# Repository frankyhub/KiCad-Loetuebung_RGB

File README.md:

<div align="center">

|[:skull:ISSUE](https://github.com/frankyhub/KiCad-Loetuebung_RGB/issues?q=is%3Aissue)|[:speech_balloon: Forum /Discussion](https://github.com/frankyhub/KiCad-Loetuebung_RGB/discussions)|[:grey_question:WiKi](https://github.com/frankyhub/KiCad-Loetuebung_RGB/wiki)||
|--|--|--|--|
| | | | |
<a href="https://github.com/frankyhub/KiCad-Loetuebung_RGB/issues">|<a href="https://github.com/frankyhub/KiCad-Loetuebung_RGB/discussions">|<a href="https://github.com/frankyhub/KiCad-Loetuebung_RGB/releases">||
|| <a href="https://github.com/frankyhub/KiCad-Loetuebung_RGB/pulse" alt="Activity">| <a href="https://github.com/frankyhub/KiCad-Loetuebung_RGB/graphs/traffic">  |<a href="https://github.com/frankyhub?tab=stars"> ||
</div>

## Fledermaus

## Seegeist

---

<div style="position:absolute; left:2cm; ">   
<ol class="breadcrumb" style="border-top: 2px solid black;border-bottom:2px solid black; height: 45px; width: 900px;"> <p align="center"><a href="#oben">nach oben</a></p></ol>
</div>  

---

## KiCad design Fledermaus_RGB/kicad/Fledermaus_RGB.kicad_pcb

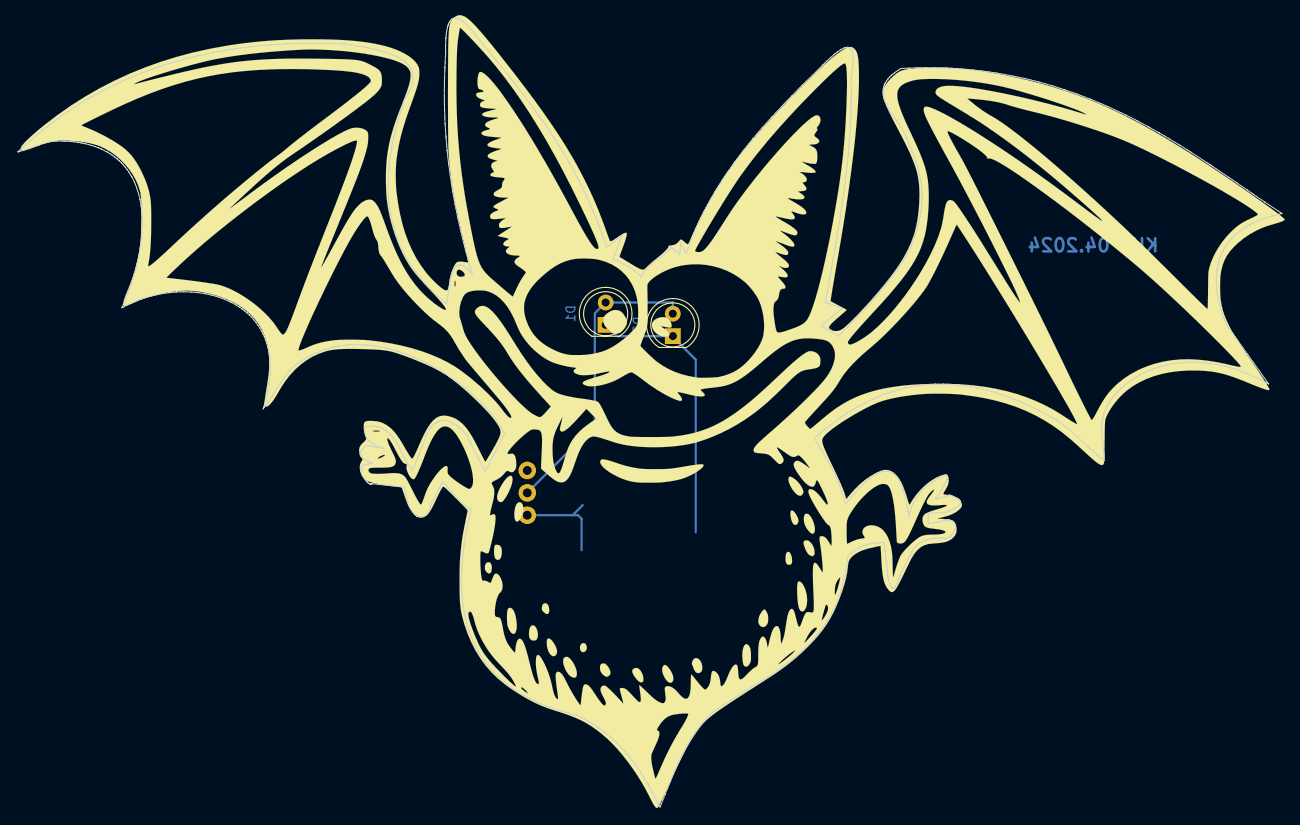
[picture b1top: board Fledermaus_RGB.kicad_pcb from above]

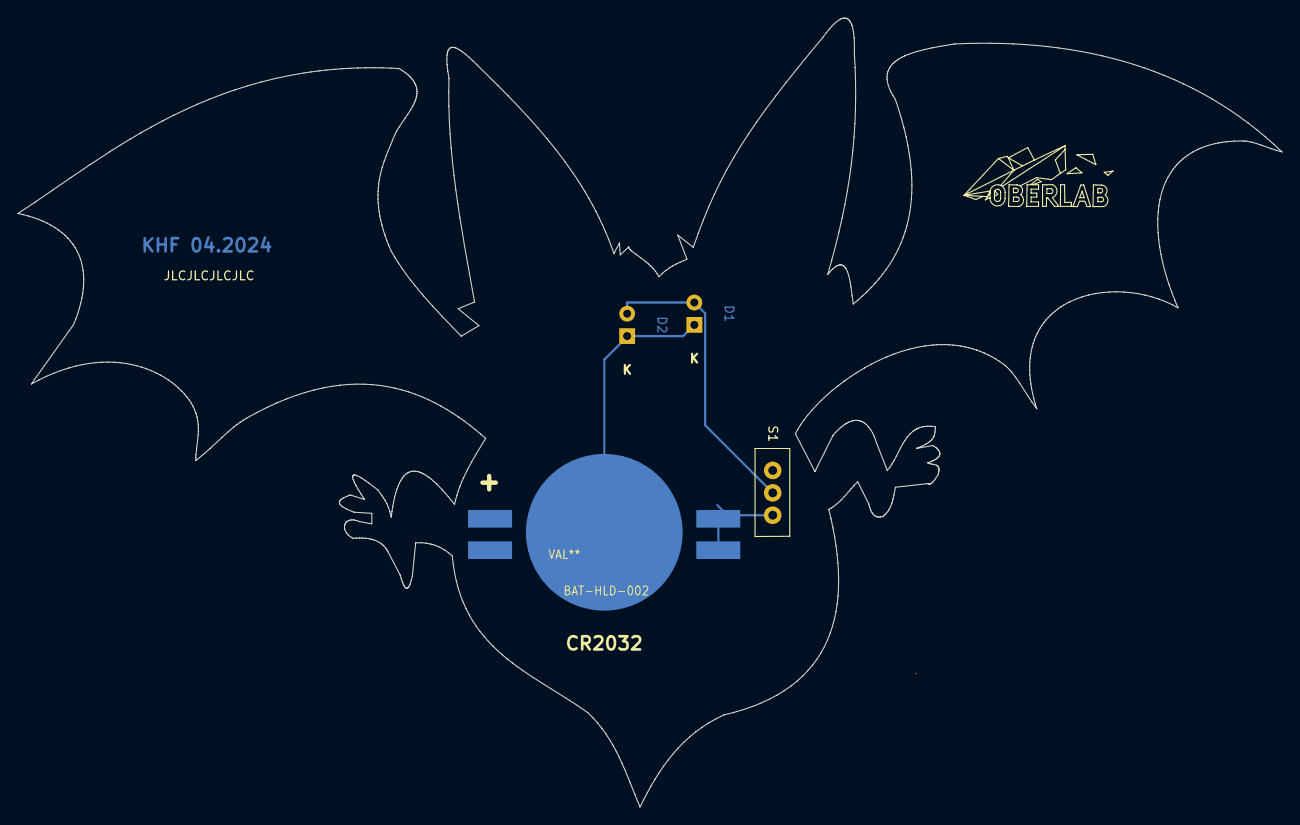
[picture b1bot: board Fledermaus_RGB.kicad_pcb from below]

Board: 2 copper layers, 143.4 x 89.5 mm, 4 parts (2 on the bottom side), 3 nets.

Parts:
BAT-HLD-002: VAL**; BAT-HLD-SMD-Blech
D1, D2: LED; LED_D5.0mm
S1: Micro_Schalter

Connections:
unnamed: BAT-HLD-002.2, D1.1, D2.1
unnamed: D1.2, D2.2, S1.2
unnamed: BAT-HLD-002.1, S1.1

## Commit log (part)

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2024-04-03 V 03.04.2024
2024-10-12 V12102024
